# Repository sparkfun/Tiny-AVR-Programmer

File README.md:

Tiny AVR Programmer
===================

[*Tiny AVR Programmer (PGM-11801)*](https://www.sparkfun.com/products/11801)

The Tiny AVR Programmer plugs directly into your USB port and provides a programming socket for the ATtiny45 and 85.

This was a collaboration with David Mellis and the MIT High Low Tech lab. 
See [Programming an ATtiny with Arduino 1.0](http://hlt.media.mit.edu/?p=1695) 
and [Using the TinyProgrammer](http://hlt.media.mit.edu/?p=1801) for more drivers and additional information.

Repository Contents
-------------------
* **/Drivers** - Signed drivers for the Tiny AVR Programmer
* **/Hardware** - Eagle design files (.brd, .sch)
* **/Production** - Production panel files (.brd)

Documentation
--------------
* **[Hookup Guide](https://learn.sparkfun.com/tutorials/tiny-avr-programmer-hookup-guide/)** - Basic hookup guide for the Programmer.
* **[SparkFun Fritzing repo](https://github.com/sparkfun/Fritzing_Parts)** - Fritzing diagrams for SparkFun products.
* **[SparkFun 3D Model repo](https://github.com/sparkfun/3D_Models)** - 3D models of SparkFun products. 

License Information
-------------------

This product is _**open source**_! 

Please review the LICENSE.md file for license information. 

If you have any questions or concerns on licensing, please visit the [SparkFun Forum](https://forum.sparkfun.com/index.php) and post a topic. For more general questions related to our programmers, please visit this section of the forum: [SparkFun Forums: PROGRAMMERS](https://forum.sparkfun.com/viewforum.php?f=104).

Distributed as-is; no warranty is given.
- Your friends at SparkFun.

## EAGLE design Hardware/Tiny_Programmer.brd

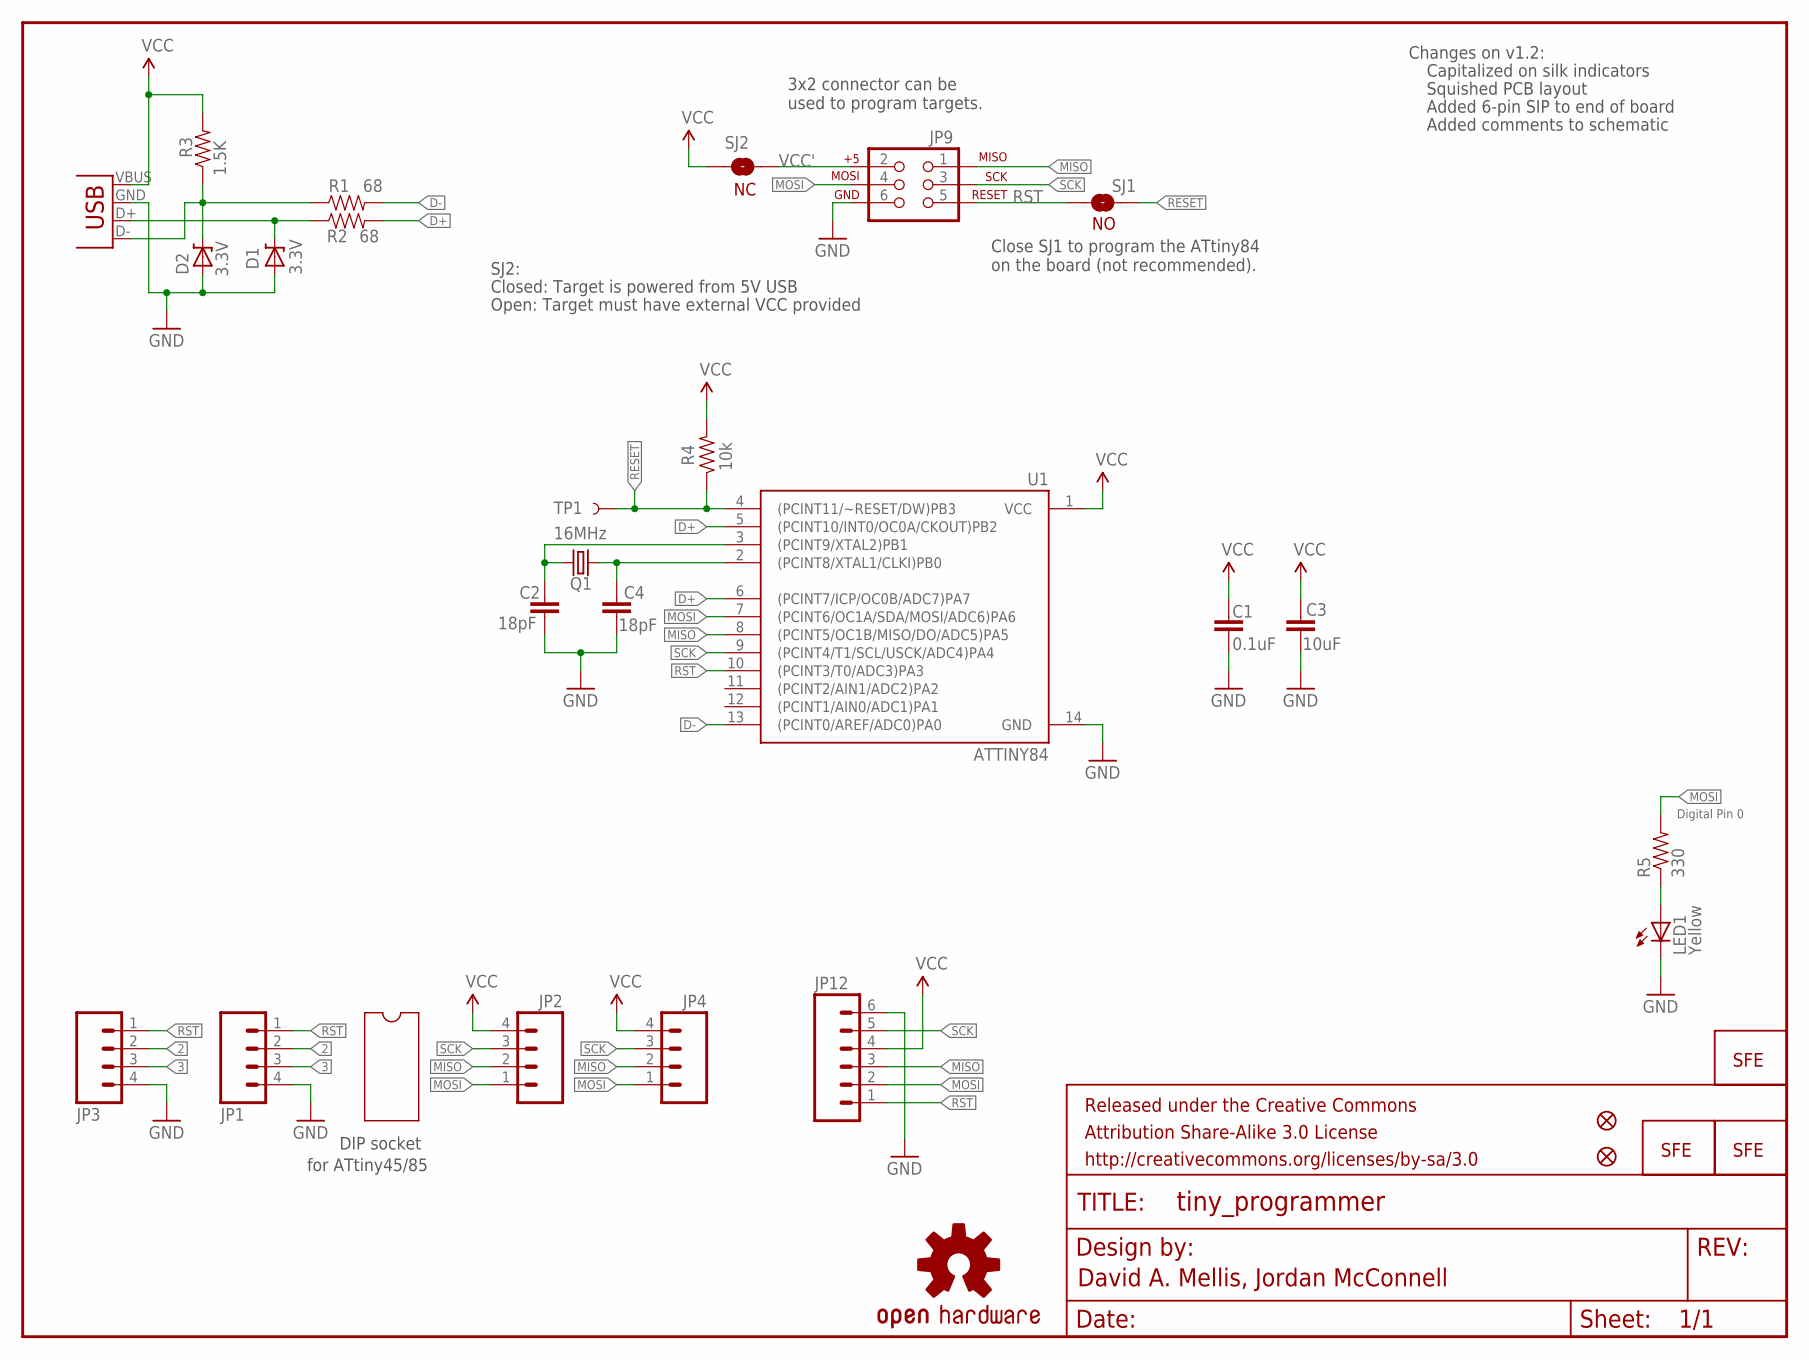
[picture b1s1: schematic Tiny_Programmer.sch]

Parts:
C1: 0.1uF; 0402-CAP
C2, C4: 18pF; 0402-CAP
C3: 10uF; 0402-CAP
D1, D2: 3.3V; SOD-323
FRAME1: FRAME-LETTER; CREATIVE_COMMONS
JP1, JP2: M04PTH; 1X04
JP3, JP4: M04SMD_STRAIGHT_COMBO; 1X04_SMD_STRAIGHT_COMBO
JP5: LOGO-SFENW2; SFE-NEW-WEB
JP6, JP11: LOGO-SFESK; SFE-LOGO-FLAME
JP7, JP8: FIDUCIALUFIDUCIAL; MICRO-FIDUCIAL
JP9: AVR_SPI_PRG_6PTH; 2X3
JP12: M06SIP; 1X06
LED1: Yellow; LED-0603
Q1: 16MHz; CRYSTAL-SMD-5X3
R1, R2: 68; 0402-RES
R3: 1.5K; 0402-RES
R4: 10k; 0402-RES
R5: 330; 0402-RES
SJ1: SOLDERJUMPERNO; SJ_2S-NO
SJ2: NC; SJ_2S
TP1: TEST-POINT3; PAD.03X.03
U1: ATTINY84; SO14
U$1: OSHW-LOGOS; OSHW-LOGO-S
X1: USB-A-H

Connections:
2: JP1.2, JP3.2
3: JP1.3, JP3.3
D+: R2.2, U1.5 ((PCINT10/INT0/OC0A/CKOUT)PB2), U1.6 ((PCINT7/ICP/OC0B/ADC7)PA7)
D-: R1.2, U1.13 ((PCINT0/AREF/ADC0)PA0)
GND: C1.2, C2.2, C3.2, C4.2, D1.2 (A), D2.2 (A), JP1.4, JP3.4, JP9.6, JP12.6, LED1.C, U1.14 (GND), X1.GND (VBUS)
MISO: JP2.2, JP4.2, JP9.1, JP12.3, U1.8 ((PCINT5/OC1B/MISO/DO/ADC5)PA5)
MOSI: JP2.1, JP4.1, JP9.4, JP12.2, R5.2, U1.7 ((PCINT6/OC1A/SDA/MOSI/ADC6)PA6)
unnamed: D2.1 (C), R1.1, R3.1, X1.D- (D+)
unnamed: D1.1 (C), R2.1, X1.D+ (D-)
unnamed: C2.1, Q1.3 (2), U1.3 ((PCINT9/XTAL2)PB1)
unnamed: C4.1, Q1.1, U1.2 ((PCINT8/XTAL1/CLKI)PB0)
unnamed: LED1.A, R5.1
RESET: R4.1, SJ1.1, TP1.P$1, U1.4 ((PCINT11/~RESET/DW)PB3)
RST: JP1.1, JP3.1, JP9.5, JP12.1, SJ1.2, U1.10 ((PCINT3/T0/ADC3)PA3)
SCK: JP2.3, JP4.3, JP9.3, JP12.5, U1.9 ((PCINT4/T1/SCL/USCK/ADC4)PA4)
VCC: C1.1, C3.1, JP2.4, JP4.4, JP12.4, R3.2, R4.2, SJ2.1, U1.1 (VCC), X1.VBUS (GND)
VCC': JP9.2, SJ2.2

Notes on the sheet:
David A. Mellis, Jordan McConnell
Digital Pin 0
Changes on v1.2:
Capitalized on silk indicators
DIP socket
for ATtiny45/85
3x2 connector can be used to program targets.
Close SJ1 to program the ATtiny84 on the board (not recommended).
Closed: Target is powered from 5V USB
Open: Target must have external VCC provided
SJ2:
Squished PCB layout
Added 6-pin SIP to end of board
Added comments to schematic

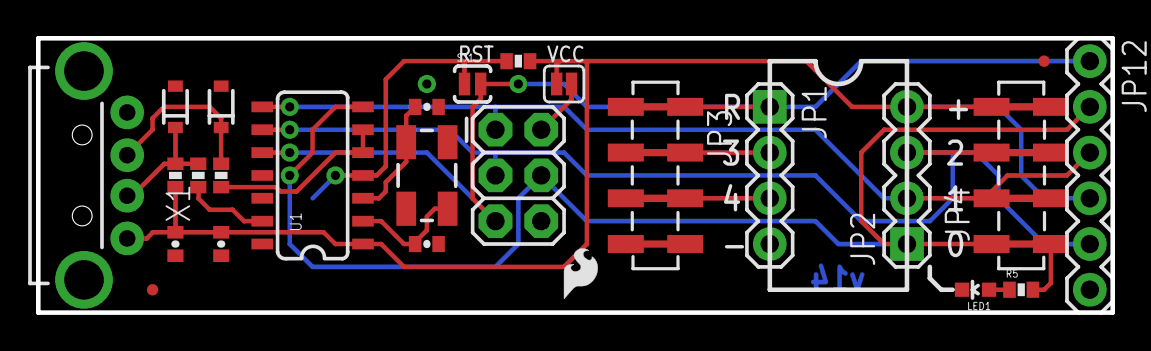
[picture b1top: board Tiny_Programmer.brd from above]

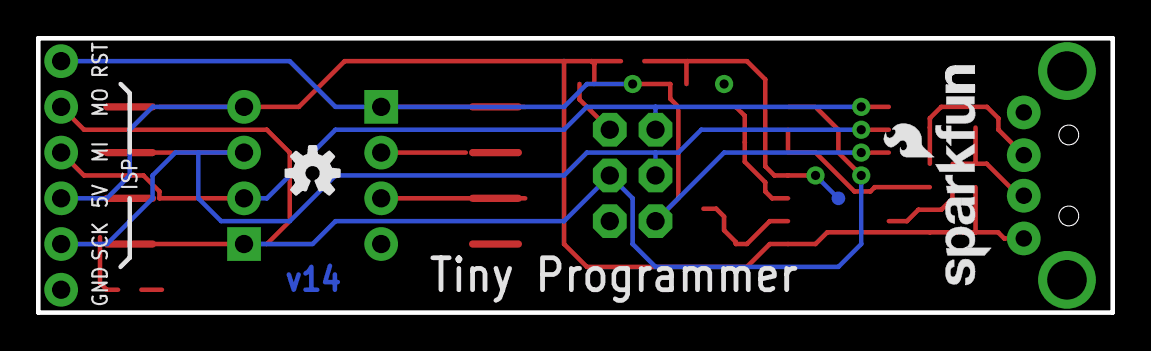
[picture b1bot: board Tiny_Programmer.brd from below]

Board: 2 copper layers, 59.7 x 15.2 mm, 31 parts (4 on the bottom side), 17 nets.

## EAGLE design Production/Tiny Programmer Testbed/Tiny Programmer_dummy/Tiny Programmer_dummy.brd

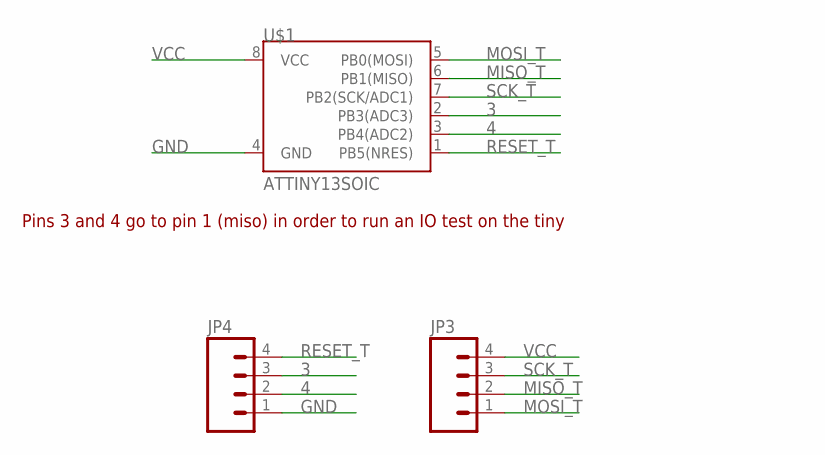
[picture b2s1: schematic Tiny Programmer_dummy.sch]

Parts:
JP3, JP4: M04PTH; 1X04
U$1: ATTINY13SOIC; SO08

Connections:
3: JP4.3, U$1.2 (PB3(ADC3))
4: JP4.2, U$1.3 (PB4(ADC2))
GND: JP4.1, U$1.4 (GND)
MISO_T: JP3.2, U$1.6 (PB1(MISO))
MOSI_T: JP3.1, U$1.5 (PB0(MOSI))
RESET_T: JP4.4, U$1.1 (PB5(NRES))
SCK_T: JP3.3, U$1.7 (PB2(SCK/ADC1))
VCC: JP3.4, U$1.8 (VCC)

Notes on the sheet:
Pins 3 and 4 go to pin 1 (miso) in order to run an IO test on the tiny

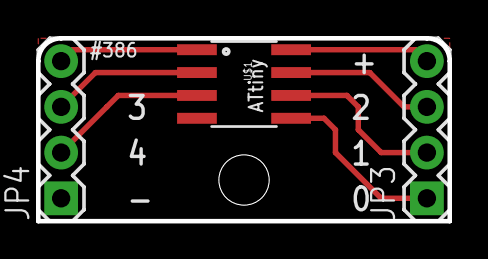
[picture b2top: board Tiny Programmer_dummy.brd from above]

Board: 2 copper layers, 22.9 x 10.2 mm, 4 parts (0 on the bottom side), 8 nets.

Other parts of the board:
U$2: STAND-OFF-TIGHTER

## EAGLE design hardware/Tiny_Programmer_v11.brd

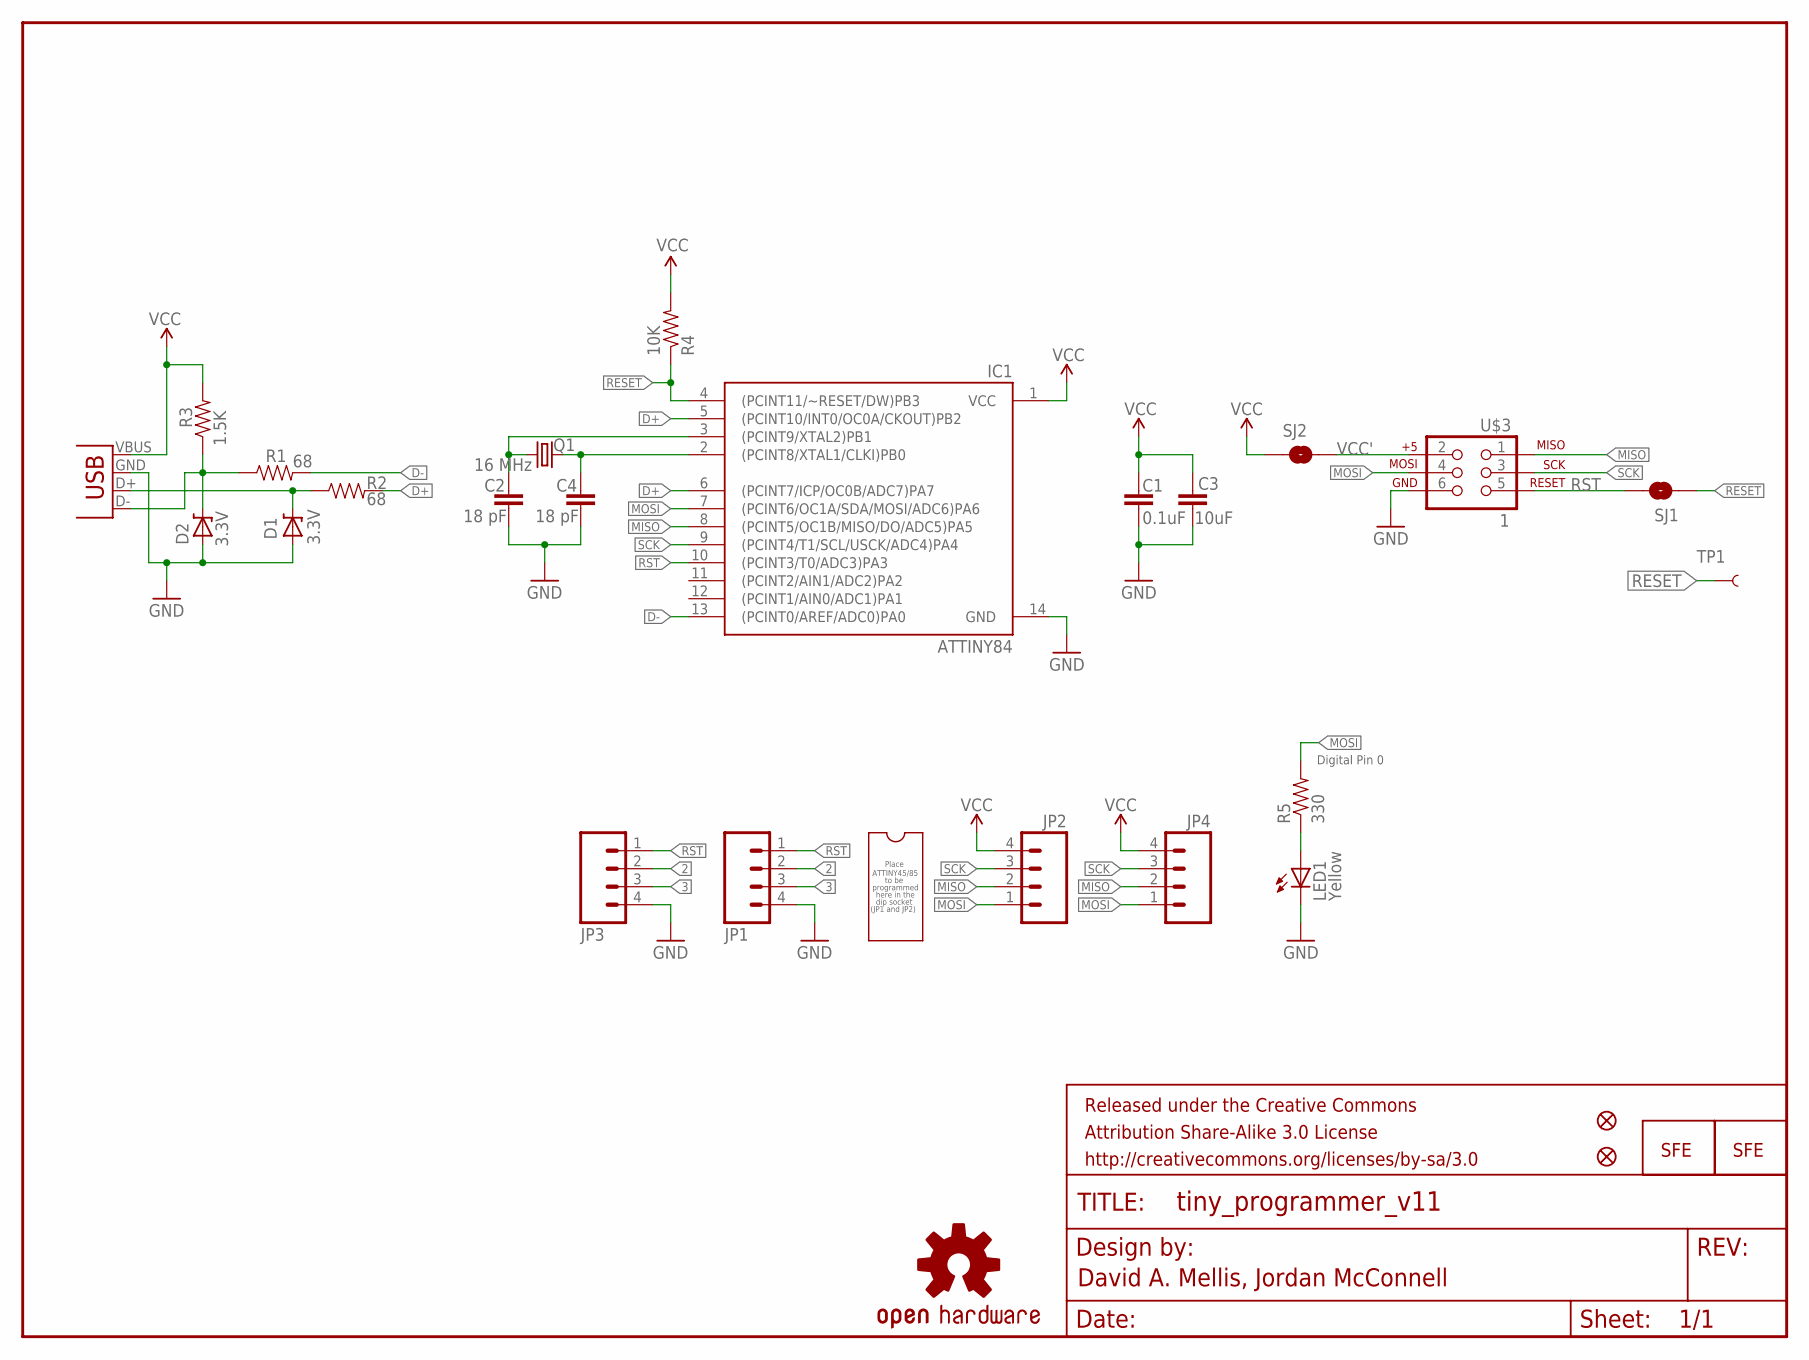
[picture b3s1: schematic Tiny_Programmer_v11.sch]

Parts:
C1: 0.1uF; 0402-CAP
C2, C4: 18 pF; 0402-CAP
C3: 10uF; 0402-CAP
D1, D2: 3.3V; SOD-323
FRAME1: FRAME-LETTER; CREATIVE_COMMONS
IC1: ATTINY84; SO14
JP1, JP2: M04PTH; 1X04
JP3, JP4: M04SMD_STRAIGHT_COMBO; 1X04_SMD_STRAIGHT_COMBO
JP5: LOGO-SFENEW; SFE-NEW-WEBLOGO
JP6: LOGO-SFESK; SFE-LOGO-FLAME
JP7, JP8: FIDUCIALUFIDUCIAL; MICRO-FIDUCIAL
LED1: Yellow; LED-0603
Q1: 16 MHz; CRYSTAL-SMD-5X3
R1, R2: 68; 0402-RES
R3: 1.5K; 0402-RES
R4: 10K; 0402-RES
R5: 330; 0402-RES
SJ1: SOLDERJUMPERNO; SJ_2S-NO
SJ2: SOLDERJUMPERNC; SJ_2S
TP1: TEST-POINT3; PAD.03X.03
U$1: OSHW-LOGOS; OSHW-LOGO-S
U$3: 1; 2X3
X1: USB-A-H

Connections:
2: JP1.2, JP3.2
3: JP1.3, JP3.3
D+: IC1.5 ((PCINT10/INT0/OC0A/CKOUT)PB2), IC1.6 ((PCINT7/ICP/OC0B/ADC7)PA7), R2.2
D-: IC1.13 ((PCINT0/AREF/ADC0)PA0), R1.2
GND: C1.2, C2.2, C3.2, C4.2, D1.2 (A), D2.2 (A), IC1.14 (GND), JP1.4, JP3.4, LED1.C, U$3.6, X1.GND (VBUS)
MISO: IC1.8 ((PCINT5/OC1B/MISO/DO/ADC5)PA5), JP2.2, JP4.2, U$3.1
MOSI: IC1.7 ((PCINT6/OC1A/SDA/MOSI/ADC6)PA6), JP2.1, JP4.1, R5.2, U$3.4
unnamed: D2.1 (C), R1.1, R3.1, X1.D- (D+)
unnamed: D1.1 (C), R2.1, X1.D+ (D-)
unnamed: C2.1, IC1.3 ((PCINT9/XTAL2)PB1), Q1.3 (2)
unnamed: C4.1, IC1.2 ((PCINT8/XTAL1/CLKI)PB0), Q1.1
unnamed: LED1.A, R5.1
RESET: IC1.4 ((PCINT11/~RESET/DW)PB3), R4.1, SJ1.1, TP1.P$1
RST: IC1.10 ((PCINT3/T0/ADC3)PA3), JP1.1, JP3.1, SJ1.2, U$3.5
SCK: IC1.9 ((PCINT4/T1/SCL/USCK/ADC4)PA4), JP2.3, JP4.3, U$3.3
VCC: C1.1, C3.1, IC1.1 (VCC), JP2.4, JP4.4, R3.2, R4.2, SJ2.1, X1.VBUS (GND)
VCC': SJ2.2, U$3.2

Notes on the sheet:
David A. Mellis, Jordan McConnell
ATTINY45/85
Place
to be
programmed
here in the
(JP1 and JP2)
Digital Pin 0
dip socket

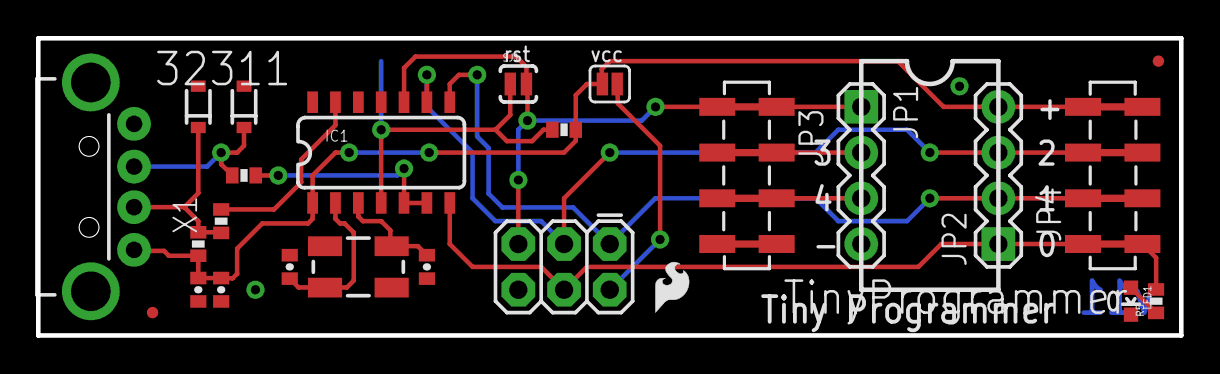
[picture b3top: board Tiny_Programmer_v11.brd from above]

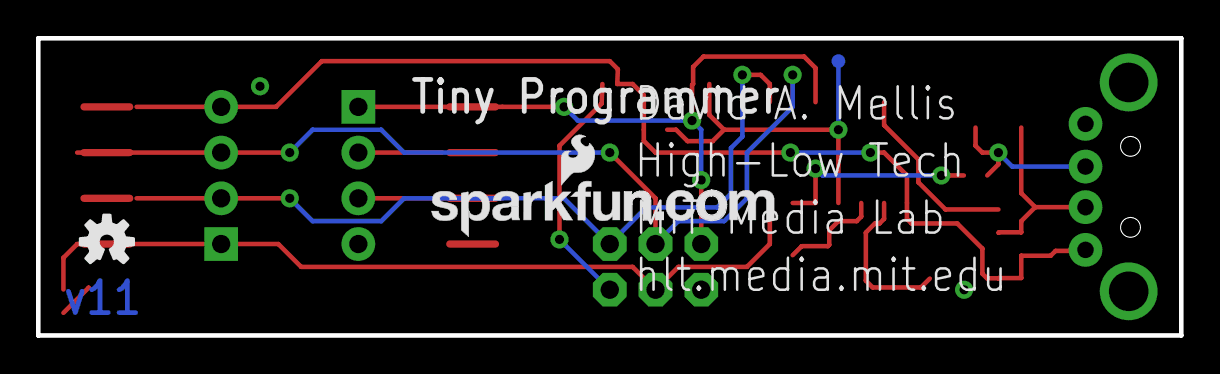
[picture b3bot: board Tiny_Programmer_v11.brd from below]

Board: 2 copper layers, 63.5 x 16.5 mm, 29 parts (3 on the bottom side), 17 nets.

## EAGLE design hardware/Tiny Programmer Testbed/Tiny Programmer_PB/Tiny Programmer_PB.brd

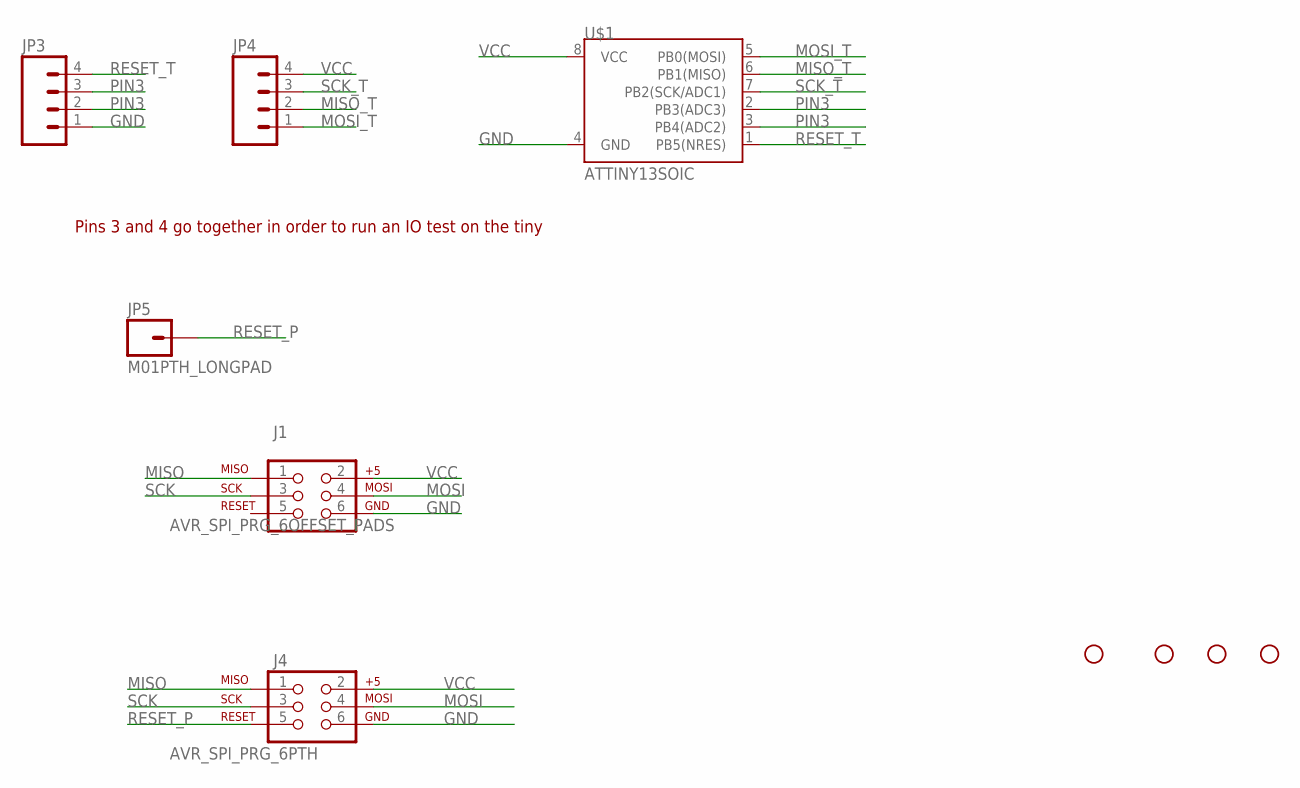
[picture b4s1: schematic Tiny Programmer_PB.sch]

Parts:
J1: AVR_SPI_PRG_6OFFSET_PADS; 2X3_OFFSET
J4: AVR_SPI_PRG_6PTH; 2X3
JP1, JP2, JP8, JP9: STAND-OFFTIGHTER; STAND-OFF-TIGHTER
JP3, JP4: M04LONGPADS; 1X04_LONGPADS
JP5: M01PTH_LONGPAD; 1X01_LONGPAD
U$1: ATTINY13SOIC; SO08

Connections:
GND: J1.6, J4.6, JP3.1, U$1.4 (GND)
MISO: J1.1, J4.1
MISO_T: JP4.2, U$1.6 (PB1(MISO))
MOSI: J1.4, J4.4
MOSI_T: JP4.1, U$1.5 (PB0(MOSI))
PIN3: JP3.2, JP3.3, U$1.2 (PB3(ADC3)), U$1.3 (PB4(ADC2))
RESET_P: J4.5, JP5.1
RESET_T: JP3.4, U$1.1 (PB5(NRES))
SCK: J1.3, J4.3
SCK_T: JP4.3, U$1.7 (PB2(SCK/ADC1))
VCC: J1.2, J4.2, JP4.4, U$1.8 (VCC)

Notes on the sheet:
Pins 3 and 4 go together in order to run an IO test on the tiny

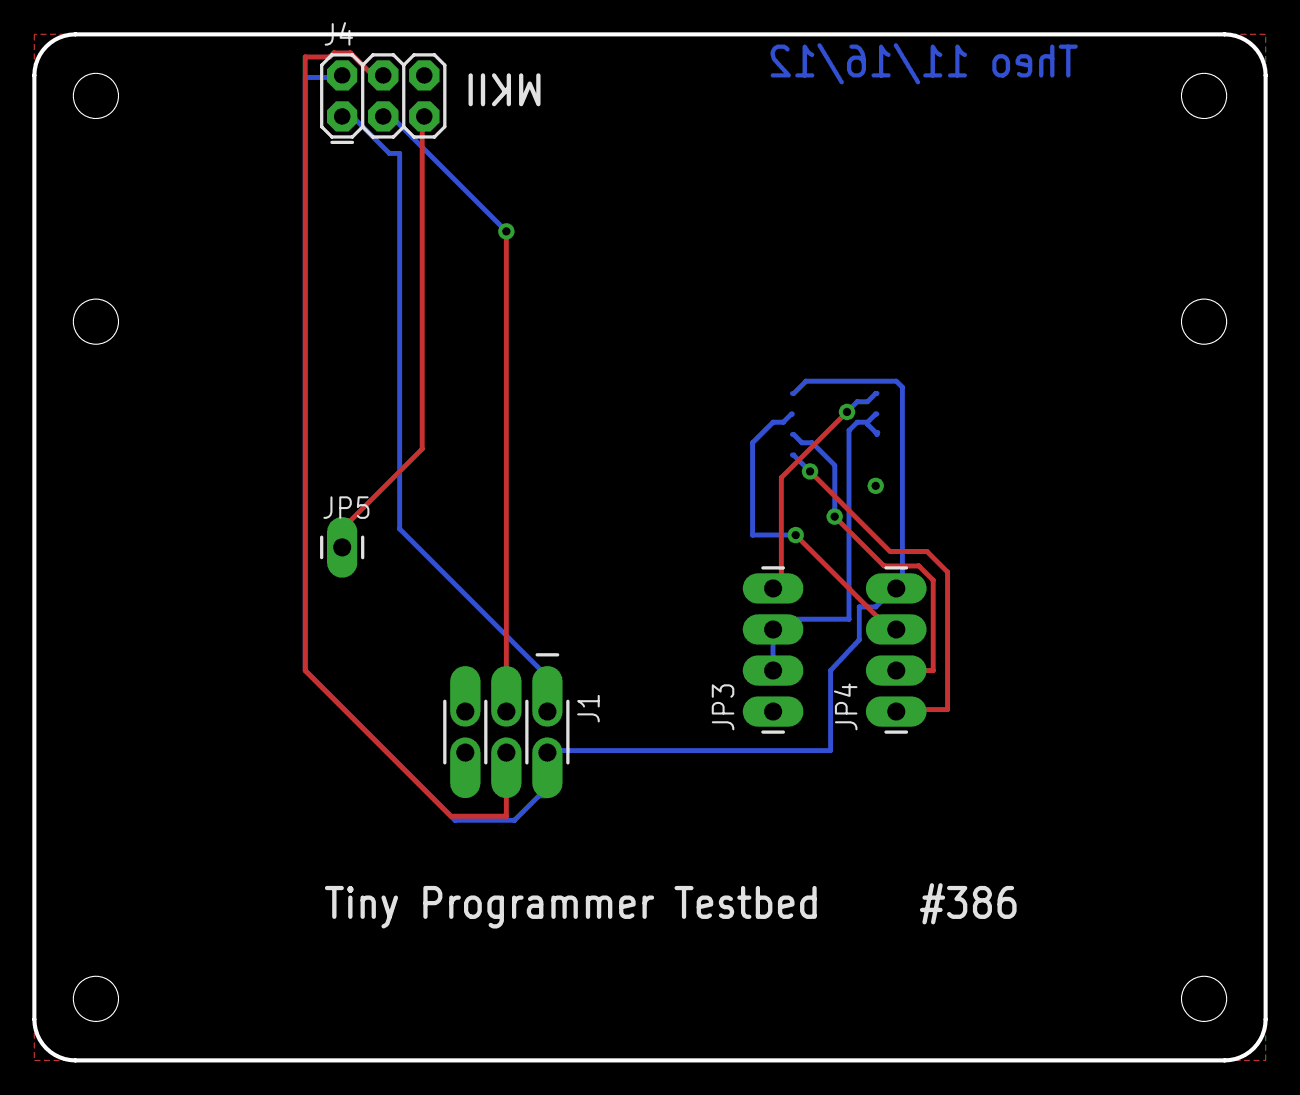
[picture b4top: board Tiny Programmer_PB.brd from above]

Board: 2 copper layers, 76.2 x 63.5 mm, 12 parts (1 on the bottom side), 11 nets.

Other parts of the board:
JP7, JP10: STAND-OFFTIGHTER; STAND-OFF-TIGHTER

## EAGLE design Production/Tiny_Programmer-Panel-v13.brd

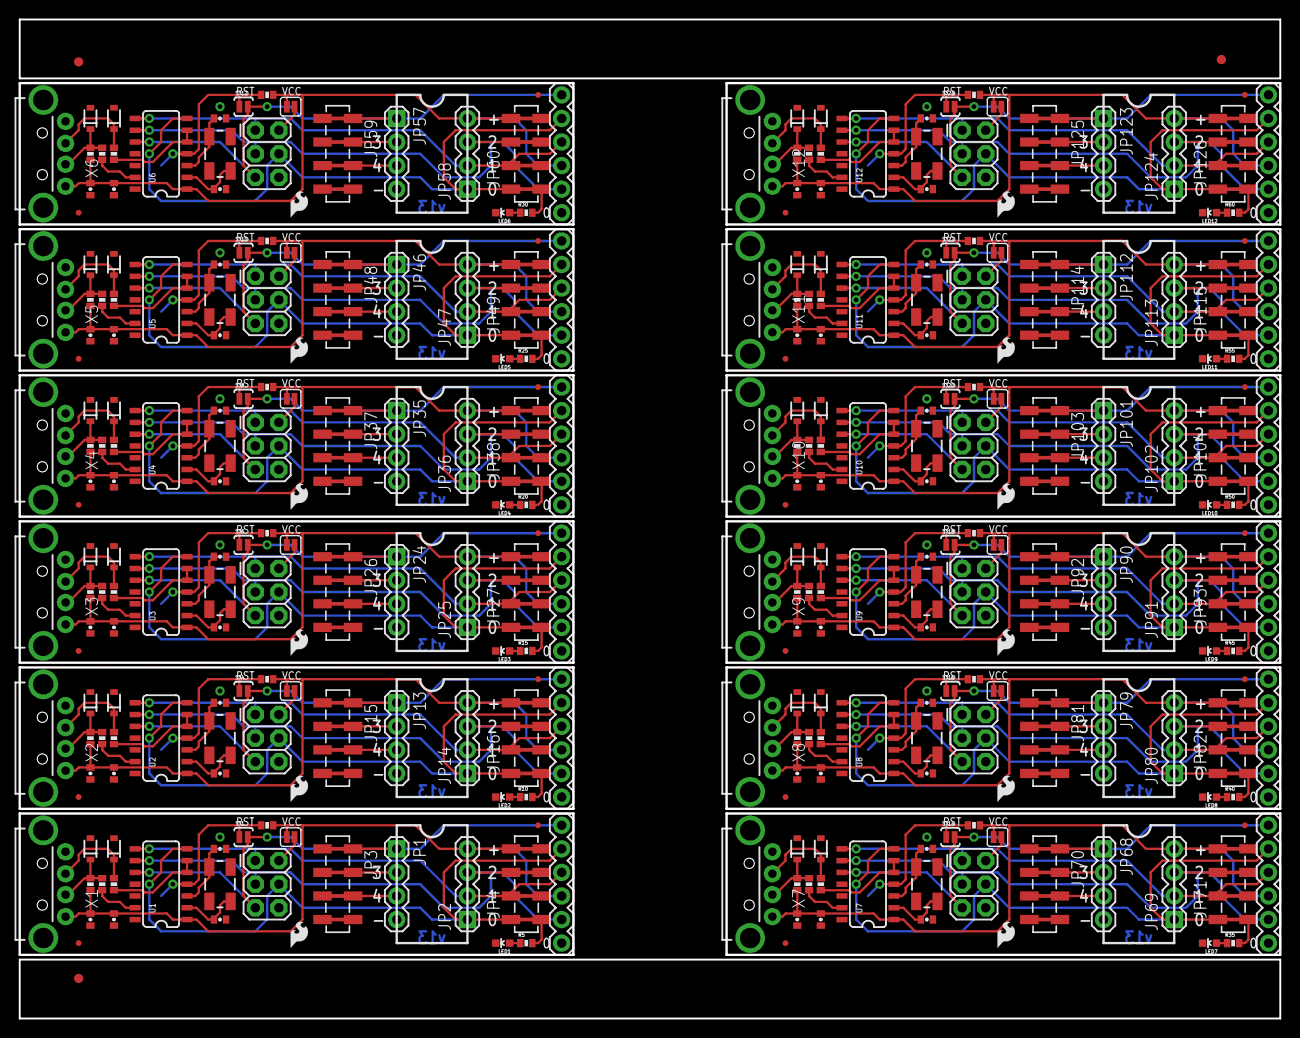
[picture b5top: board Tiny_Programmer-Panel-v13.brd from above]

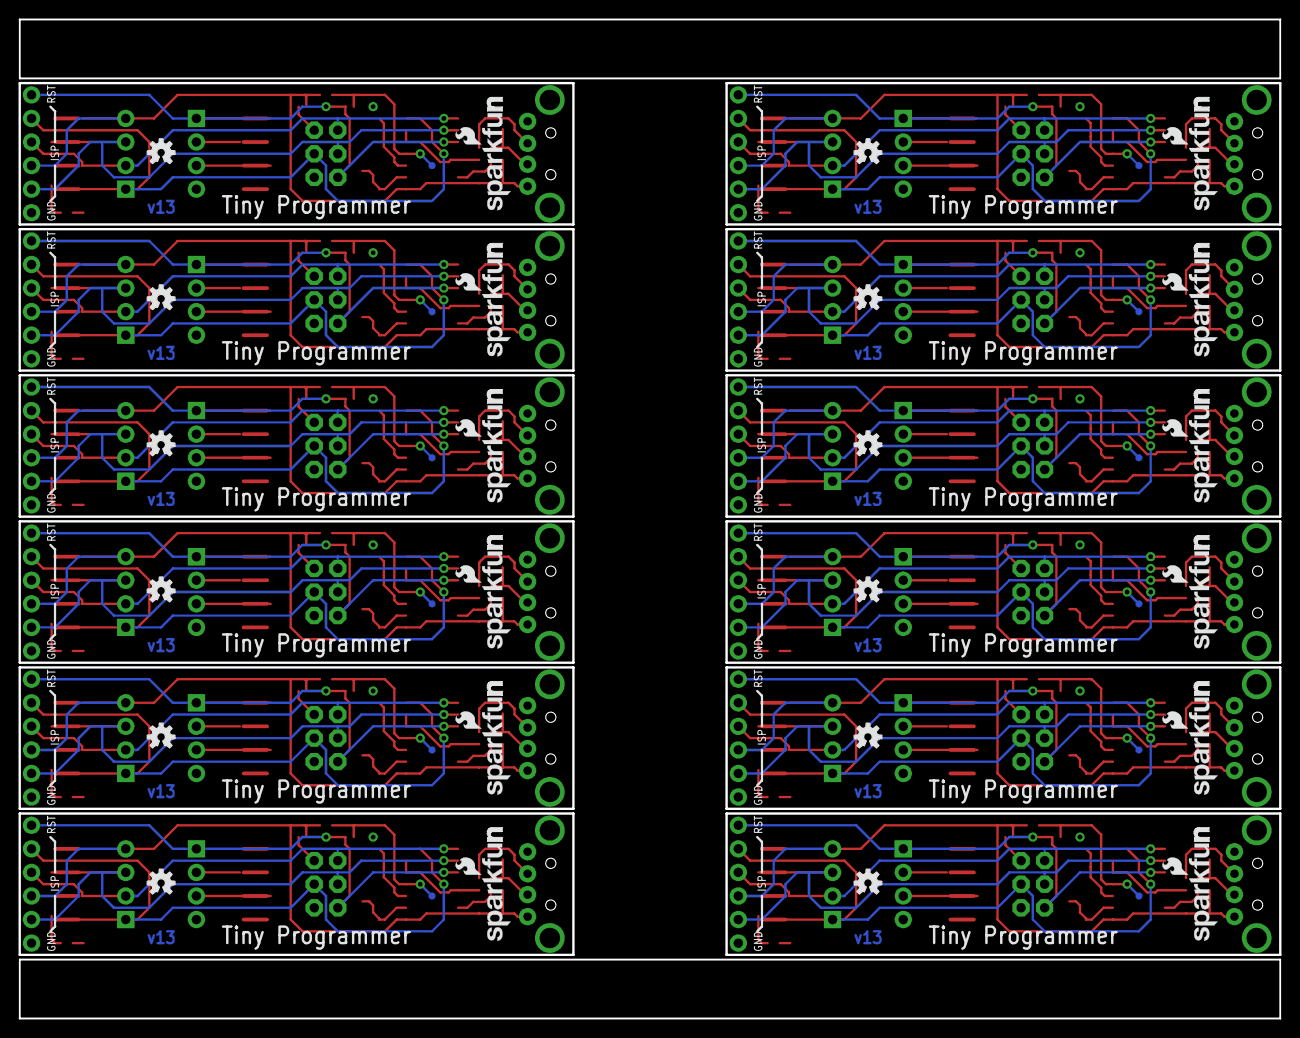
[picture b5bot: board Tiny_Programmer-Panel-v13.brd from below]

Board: 2 copper layers, 135.9 x 107.6 mm, 363 parts (48 on the bottom side), 204 nets.

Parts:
C1, C5, C9, C13, C17, C21, C25, C29, C33, C37, C41, C45: 0.1uF; 0402-CAP
C2, C4, C7, C8, C11, C12, C15, C16, C19, C20, C23, C24, C27, C28, C31, C32, C35, C36, C39, C40, C43, C44, C47, C48: 18pF; 0402-CAP
C3, C6, C10, C14, C18, C22, C26, C30, C34, C38, C42, C46: 10uF; 0402-CAP
D1, D2, D3, D4, D5, D6, D7, D8, D9, D10, D11, D12, D13, D14, D15, D16, D17, D18, D19, D20, D21, D22, D23, D24: 3.3V; SOD-323
E$1, E$3, E$4: FIDUCIAL-1X2
JP1, JP2, JP13, JP14, JP24, JP25, JP35, JP36, JP46, JP47, JP57, JP58, JP68, JP69, JP79, JP80, JP90, JP91, JP101, JP102, JP112, JP113, JP123, JP124: 1X04
JP3, JP4, JP15, JP16, JP26, JP27, JP37, JP38, JP48, JP49, JP59, JP60, JP70, JP71, JP81, JP82, JP92, JP93, JP103, JP104, JP114, JP115, JP125, JP126: 1X04_SMD_STRAIGHT_COMBO
JP5, JP17, JP28, JP39, JP50, JP61, JP72, JP83, JP94, JP105, JP116, JP127: LOGO-SFENW2; SFE-NEW-WEB
JP6, JP11, JP18, JP21, JP29, JP32, JP40, JP43, JP51, JP54, JP62, JP65, JP73, JP76, JP84, JP87, JP95, JP98, JP106, JP109, JP117, JP120, JP128, JP131: LOGO-SFESK; SFE-LOGO-FLAME
JP7, JP8, JP19, JP20, JP30, JP31, JP41, JP42, JP52, JP53, JP63, JP64, JP74, JP75, JP85, JP86, JP96, JP97, JP107, JP108, JP118, JP119, JP129, JP130: FIDUCIALUFIDUCIAL; MICRO-FIDUCIAL
JP9, JP10, JP23, JP34, JP45, JP56, JP67, JP78, JP89, JP100, JP111, JP122: 2X3
JP12, JP22, JP33, JP44, JP55, JP66, JP77, JP88, JP99, JP110, JP121, JP132: 1X06
LED1, LED2, LED3, LED4, LED5, LED6, LED7, LED8, LED9, LED10, LED11, LED12: Yellow; LED-0603
Q1, Q2, Q3, Q4, Q5, Q6, Q7, Q8, Q9, Q10, Q11, Q12: 16MHz; CRYSTAL-SMD-5X3
R1, R2, R6, R7, R11, R12, R16, R17, R21, R22, R26, R27, R31, R32, R36, R37, R41, R42, R46, R47, R51, R52, R56, R57: 68; 0402-RES
R3, R8, R13, R18, R23, R28, R33, R38, R43, R48, R53, R58: 1.5K; 0402-RES
R4, R9, R14, R19, R24, R29, R34, R39, R44, R49, R54, R59: 10k; 0402-RES
R5, R10, R15, R20, R25, R30, R35, R40, R45, R50, R55, R60: 330; 0402-RES
SJ1, SJ4, SJ6, SJ8, SJ10, SJ12, SJ14, SJ16, SJ18, SJ20, SJ22, SJ24: SOLDERJUMPERNO; SJ_2S-NO
SJ2, SJ3, SJ5, SJ7, SJ9, SJ11, SJ13, SJ15, SJ17, SJ19, SJ21, SJ23: NC; SJ_2S
TP1, TP2, TP3, TP4, TP5, TP6, TP7, TP8, TP9, TP10, TP11, TP12: TEST-POINT3; PAD.03X.03
U1, U2, U3, U4, U5, U6, U7, U8, U9, U10, U11, U12: ATTINY84; SO14
U$1, U$2, U$3, U$4, U$5, U$6, U$7, U$8, U$9, U$10, U$11, U$12: OSHW-LOGOS; OSHW-LOGO-S
X1, X2, X3, X4, X5, X6, X7, X8, X9, X10, X11, X12: USB-A-H

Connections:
1: JP13.3, JP15.3
2: JP1.2, JP3.2
3: JP1.3, JP3.3
4: JP13.2, JP15.2
5: JP24.3, JP26.3
6: JP24.2, JP26.2
7: JP35.3, JP37.3
8: JP35.2, JP37.2
9: JP46.3, JP48.3
10: JP46.2, JP48.2
11: JP57.3, JP59.3
12: JP57.2, JP59.2
13: JP68.3, JP70.3
14: JP68.2, JP70.2
15: JP79.3, JP81.3
16: JP79.2, JP81.2
17: JP90.3, JP92.3
18: JP90.2, JP92.2
19: JP101.3, JP103.3
20: JP101.2, JP103.2
21: JP112.3, JP114.3
22: JP112.2, JP114.2
23: JP123.3, JP125.3
24: JP123.2, JP125.2
D+: R2.2, U1.5, U1.6
D+1: R7.2, U2.5, U2.6
D+2: R12.2, U3.5, U3.6
D+3: R17.2, U4.5, U4.6
D+4: R22.2, U5.5, U5.6
D+5: R27.2, U6.5, U6.6
D+6: R32.2, U7.5, U7.6
D+7: R37.2, U8.5, U8.6
D+8: R42.2, U9.5, U9.6
D+9: R47.2, U10.5, U10.6
D+10: R52.2, U11.5, U11.6
D+11: R57.2, U12.5, U12.6
D-: R1.2, U1.13
D-1: R6.2, U2.13
D-2: R11.2, U3.13
D-3: R16.2, U4.13
D-4: R21.2, U5.13
D-5: R26.2, U6.13
D-6: R31.2, U7.13
D-7: R36.2, U8.13
D-8: R41.2, U9.13
D-9: R46.2, U10.13
D-10: R51.2, U11.13
D-11: R56.2, U12.13
GND: C1.2, C2.2, C3.2, C4.2, D1.2, D2.2, JP1.4, JP3.4, JP9.6, JP12.6, LED1.C, U1.14, X1.GND
GND1: C5.2, C6.2, C7.2, C8.2, D3.2, D4.2, JP10.6, JP13.4, JP15.4, JP22.6, LED2.C, U2.14, X2.GND
GND2: C9.2, C10.2, C11.2, C12.2, D5.2, D6.2, JP23.6, JP24.4, JP26.4, JP33.6, LED3.C, U3.14, X3.GND
GND3: C13.2, C14.2, C15.2, C16.2, D7.2, D8.2, JP34.6, JP35.4, JP37.4, JP44.6, LED4.C, U4.14, X4.GND
GND4: C17.2, C18.2, C19.2, C20.2, D9.2, D10.2, JP45.6, JP46.4, JP48.4, JP55.6, LED5.C, U5.14, X5.GND
GND5: C21.2, C22.2, C23.2, C24.2, D11.2, D12.2, JP56.6, JP57.4, JP59.4, JP66.6, LED6.C, U6.14, X6.GND
GND6: C25.2, C26.2, C27.2, C28.2, D13.2, D14.2, JP67.6, JP68.4, JP70.4, JP77.6, LED7.C, U7.14, X7.GND
GND7: C29.2, C30.2, C31.2, C32.2, D15.2, D16.2, JP78.6, JP79.4, JP81.4, JP88.6, LED8.C, U8.14, X8.GND
GND8: C33.2, C34.2, C35.2, C36.2, D17.2, D18.2, JP89.6, JP90.4, JP92.4, JP99.6, LED9.C, U9.14, X9.GND
GND9: C37.2, C38.2, C39.2, C40.2, D19.2, D20.2, JP100.6, JP101.4, JP103.4, JP110.6, LED10.C, U10.14, X10.GND
GND10: C41.2, C42.2, C43.2, C44.2, D21.2, D22.2, JP111.6, JP112.4, JP114.4, JP121.6, LED11.C, U11.14, X11.GND
GND11: C45.2, C46.2, C47.2, C48.2, D23.2, D24.2, JP122.6, JP123.4, JP125.4, JP132.6, LED12.C, U12.14, X12.GND
MISO: JP2.2, JP4.2, JP9.1, JP12.3, U1.8
MISO1: JP10.1, JP14.2, JP16.2, JP22.3, U2.8
MISO2: JP23.1, JP25.2, JP27.2, JP33.3, U3.8
MISO3: JP34.1, JP36.2, JP38.2, JP44.3, U4.8
MISO4: JP45.1, JP47.2, JP49.2, JP55.3, U5.8
MISO5: JP56.1, JP58.2, JP60.2, JP66.3, U6.8
MISO6: JP67.1, JP69.2, JP71.2, JP77.3, U7.8
MISO7: JP78.1, JP80.2, JP82.2, JP88.3, U8.8
MISO8: JP89.1, JP91.2, JP93.2, JP99.3, U9.8
MISO9: JP100.1, JP102.2, JP104.2, JP110.3, U10.8
MISO10: JP111.1, JP113.2, JP115.2, JP121.3, U11.8
MISO11: JP122.1, JP124.2, JP126.2, JP132.3, U12.8
MOSI: JP2.1, JP4.1, JP9.4, JP12.2, R5.2, U1.7
MOSI1: JP10.4, JP14.1, JP16.1, JP22.2, R10.2, U2.7
MOSI2: JP23.4, JP25.1, JP27.1, JP33.2, R15.2, U3.7
MOSI3: JP34.4, JP36.1, JP38.1, JP44.2, R20.2, U4.7
MOSI4: JP45.4, JP47.1, JP49.1, JP55.2, R25.2, U5.7
MOSI5: JP56.4, JP58.1, JP60.1, JP66.2, R30.2, U6.7
MOSI6: JP67.4, JP69.1, JP71.1, JP77.2, R35.2, U7.7
MOSI7: JP78.4, JP80.1, JP82.1, JP88.2, R40.2, U8.7
MOSI8: JP89.4, JP91.1, JP93.1, JP99.2, R45.2, U9.7
MOSI9: JP100.4, JP102.1, JP104.1, JP110.2, R50.2, U10.7
MOSI10: JP111.4, JP113.1, JP115.1, JP121.2, R55.2, U11.7
MOSI11: JP122.4, JP124.1, JP126.1, JP132.2, R60.2, U12.7
unnamed: D2.1, R1.1, R3.1, X1.D-
unnamed: D1.1, R2.1, X1.D+
unnamed: C2.1, Q1.3, U1.3
unnamed: C4.1, Q1.1, U1.2
unnamed: LED1.A, R5.1
unnamed: D4.1, R6.1, R8.1, X2.D-
unnamed: D3.1, R7.1, X2.D+
unnamed: C7.1, Q2.3, U2.3
unnamed: C8.1, Q2.1, U2.2
unnamed: LED2.A, R10.1
unnamed: D6.1, R11.1, R13.1, X3.D-
unnamed: D5.1, R12.1, X3.D+
unnamed: C11.1, Q3.3, U3.3
unnamed: C12.1, Q3.1, U3.2
unnamed: LED3.A, R15.1
unnamed: D8.1, R16.1, R18.1, X4.D-
unnamed: D7.1, R17.1, X4.D+
unnamed: C15.1, Q4.3, U4.3
unnamed: C16.1, Q4.1, U4.2
unnamed: LED4.A, R20.1
unnamed: D10.1, R21.1, R23.1, X5.D-
unnamed: D9.1, R22.1, X5.D+
unnamed: C19.1, Q5.3, U5.3
unnamed: C20.1, Q5.1, U5.2
unnamed: LED5.A, R25.1
unnamed: D12.1, R26.1, R28.1, X6.D-
unnamed: D11.1, R27.1, X6.D+
unnamed: C23.1, Q6.3, U6.3
unnamed: C24.1, Q6.1, U6.2
unnamed: LED6.A, R30.1
unnamed: D14.1, R31.1, R33.1, X7.D-
unnamed: D13.1, R32.1, X7.D+
unnamed: C27.1, Q7.3, U7.3
unnamed: C28.1, Q7.1, U7.2
unnamed: LED7.A, R35.1
unnamed: D16.1, R36.1, R38.1, X8.D-
unnamed: D15.1, R37.1, X8.D+
unnamed: C31.1, Q8.3, U8.3
unnamed: C32.1, Q8.1, U8.2
unnamed: LED8.A, R40.1
unnamed: D18.1, R41.1, R43.1, X9.D-
unnamed: D17.1, R42.1, X9.D+
unnamed: C35.1, Q9.3, U9.3
unnamed: C36.1, Q9.1, U9.2
unnamed: LED9.A, R45.1
unnamed: D20.1, R46.1, R48.1, X10.D-
unnamed: D19.1, R47.1, X10.D+
unnamed: C39.1, Q10.3, U10.3
unnamed: C40.1, Q10.1, U10.2
unnamed: LED10.A, R50.1
unnamed: D22.1, R51.1, R53.1, X11.D-
unnamed: D21.1, R52.1, X11.D+
unnamed: C43.1, Q11.3, U11.3
unnamed: C44.1, Q11.1, U11.2
unnamed: LED11.A, R55.1
unnamed: D24.1, R56.1, R58.1, X12.D-
unnamed: D23.1, R57.1, X12.D+
unnamed: C47.1, Q12.3, U12.3
unnamed: C48.1, Q12.1, U12.2
unnamed: LED12.A, R60.1
RESET: R4.1, SJ1.1, TP1.P$1, U1.4
RESET1: R9.1, SJ4.1, TP2.P$1, U2.4
RESET2: R14.1, SJ6.1, TP3.P$1, U3.4
RESET3: R19.1, SJ8.1, TP4.P$1, U4.4
RESET4: R24.1, SJ10.1, TP5.P$1, U5.4
RESET5: R29.1, SJ12.1, TP6.P$1, U6.4
RESET6: R34.1, SJ14.1, TP7.P$1, U7.4
RESET7: R39.1, SJ16.1, TP8.P$1, U8.4
RESET8: R44.1, SJ18.1, TP9.P$1, U9.4
RESET9: R49.1, SJ20.1, TP10.P$1, U10.4
RESET10: R54.1, SJ22.1, TP11.P$1, U11.4
RESET11: R59.1, SJ24.1, TP12.P$1, U12.4
RST: JP1.1, JP3.1, JP9.5, JP12.1, SJ1.2, U1.10
RST1: JP10.5, JP13.1, JP15.1, JP22.1, SJ4.2, U2.10
RST2: JP23.5, JP24.1, JP26.1, JP33.1, SJ6.2, U3.10
RST3: JP34.5, JP35.1, JP37.1, JP44.1, SJ8.2, U4.10
RST4: JP45.5, JP46.1, JP48.1, JP55.1, SJ10.2, U5.10
RST5: JP56.5, JP57.1, JP59.1, JP66.1, SJ12.2, U6.10
RST6: JP67.5, JP68.1, JP70.1, JP77.1, SJ14.2, U7.10
RST7: JP78.5, JP79.1, JP81.1, JP88.1, SJ16.2, U8.10
RST8: JP89.5, JP90.1, JP92.1, JP99.1, SJ18.2, U9.10
RST9: JP100.5, JP101.1, JP103.1, JP110.1, SJ20.2, U10.10
RST10: JP111.5, JP112.1, JP114.1, JP121.1, SJ22.2, U11.10
RST11: JP122.5, JP123.1, JP125.1, JP132.1, SJ24.2, U12.10
SCK: JP2.3, JP4.3, JP9.3, JP12.5, U1.9
SCK1: JP10.3, JP14.3, JP16.3, JP22.5, U2.9
SCK2: JP23.3, JP25.3, JP27.3, JP33.5, U3.9
SCK3: JP34.3, JP36.3, JP38.3, JP44.5, U4.9
SCK4: JP45.3, JP47.3, JP49.3, JP55.5, U5.9
SCK5: JP56.3, JP58.3, JP60.3, JP66.5, U6.9
SCK6: JP67.3, JP69.3, JP71.3, JP77.5, U7.9
SCK7: JP78.3, JP80.3, JP82.3, JP88.5, U8.9
SCK8: JP89.3, JP91.3, JP93.3, JP99.5, U9.9
SCK9: JP100.3, JP102.3, JP104.3, JP110.5, U10.9
SCK10: JP111.3, JP113.3, JP115.3, JP121.5, U11.9
SCK11: JP122.3, JP124.3, JP126.3, JP132.5, U12.9
VCC: C1.1, C3.1, JP2.4, JP4.4, JP12.4, R3.2, R4.2, SJ2.1, U1.1, X1.VBUS
VCC1: C5.1, C6.1, JP14.4, JP16.4, JP22.4, R8.2, R9.2, SJ3.1, U2.1, X2.VBUS
VCC2: C9.1, C10.1, JP25.4, JP27.4, JP33.4, R13.2, R14.2, SJ5.1, U3.1, X3.VBUS
VCC3: C13.1, C14.1, JP36.4, JP38.4, JP44.4, R18.2, R19.2, SJ7.1, U4.1, X4.VBUS
VCC4: C17.1, C18.1, JP47.4, JP49.4, JP55.4, R23.2, R24.2, SJ9.1, U5.1, X5.VBUS
VCC5: C21.1, C22.1, JP58.4, JP60.4, JP66.4, R28.2, R29.2, SJ11.1, U6.1, X6.VBUS
VCC6: C25.1, C26.1, JP69.4, JP71.4, JP77.4, R33.2, R34.2, SJ13.1, U7.1, X7.VBUS
VCC7: C29.1, C30.1, JP80.4, JP82.4, JP88.4, R38.2, R39.2, SJ15.1, U8.1, X8.VBUS
VCC8: C33.1, C34.1, JP91.4, JP93.4, JP99.4, R43.2, R44.2, SJ17.1, U9.1, X9.VBUS
VCC9: C37.1, C38.1, JP102.4, JP104.4, JP110.4, R48.2, R49.2, SJ19.1, U10.1, X10.VBUS
VCC10: C41.1, C42.1, JP113.4, JP115.4, JP121.4, R53.2, R54.2, SJ21.1, U11.1, X11.VBUS
VCC11: C45.1, C46.1, JP124.4, JP126.4, JP132.4, R58.2, R59.2, SJ23.1, U12.1, X12.VBUS
VCC': JP9.2, SJ2.2
VCC'1: JP10.2, SJ3.2
VCC'2: JP23.2, SJ5.2
VCC'3: JP34.2, SJ7.2
VCC'4: JP45.2, SJ9.2
VCC'5: JP56.2, SJ11.2
VCC'6: JP67.2, SJ13.2
VCC'7: JP78.2, SJ15.2
VCC'8: JP89.2, SJ17.2
VCC'9: JP100.2, SJ19.2
VCC'10: JP111.2, SJ21.2
VCC'11: JP122.2, SJ23.2

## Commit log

2013-04-03 Pushed v1.2 of board. Added 6-pin SIP to edge of board.
    General PCB squishing. Not sure if the edge-mount USB will have enough
    room near the mounting holes. Need to run proto.
2013-04-03 Updated comments on schematic.
2013-04-16 Updated readme.
2013-04-17 Added gitattributes
2013-04-17 Going to new conventions.
    Remove extra eagle backup files. Remove version from eagle files (let
    github do versioning). Moved test bed files into production folder.
2013-09-23 Modifies the new 6-pin SIP to be more compatible with an FTDI.
    The new pin out should allow MOSI and MISO to bit-bang serial and
    communicate over an FTDI connection for serial debuggin.
2013-09-23 Panel Created
    Panel created in Production folder, Panels folder...
2013-09-26 Revert "Panel Created"
    This reverts commit 09fbf32834caab243eb0e1dba20c0eff250af01e.
2013-09-26 Revert "Modifies the new 6-pin SIP to be more compatible with an FTDI."
    This reverts commit e9ce5eee6c851359ce4a9d7fdec24ce809564be4.
2013-11-19 Added labels to each SIP pin. Moved 0 indicator.
2015-08-27 Added signed Windows drivers
2015-11-23 Adding version number to schematic
2015-11-23 Cleaning up repository
2015-11-23 adding untested note to readme
2019-07-11 Updat Licensing
    remove TS email... add forum link
2019-07-11 Update License Section
    Add forum link
2019-07-11 Edit

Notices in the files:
parts and their libraries:
SparkFun-Passives: Licensing: CC v3.0 Share-Alike You are welcome to use this library for commercial purposes.
SparkFun-Aesthetics: Released under the Creative Commons Attribution Share-Alike 3.0 License
SparkFun-Aesthetics: http://creativecommons.org/licenses/by-sa/3.0
